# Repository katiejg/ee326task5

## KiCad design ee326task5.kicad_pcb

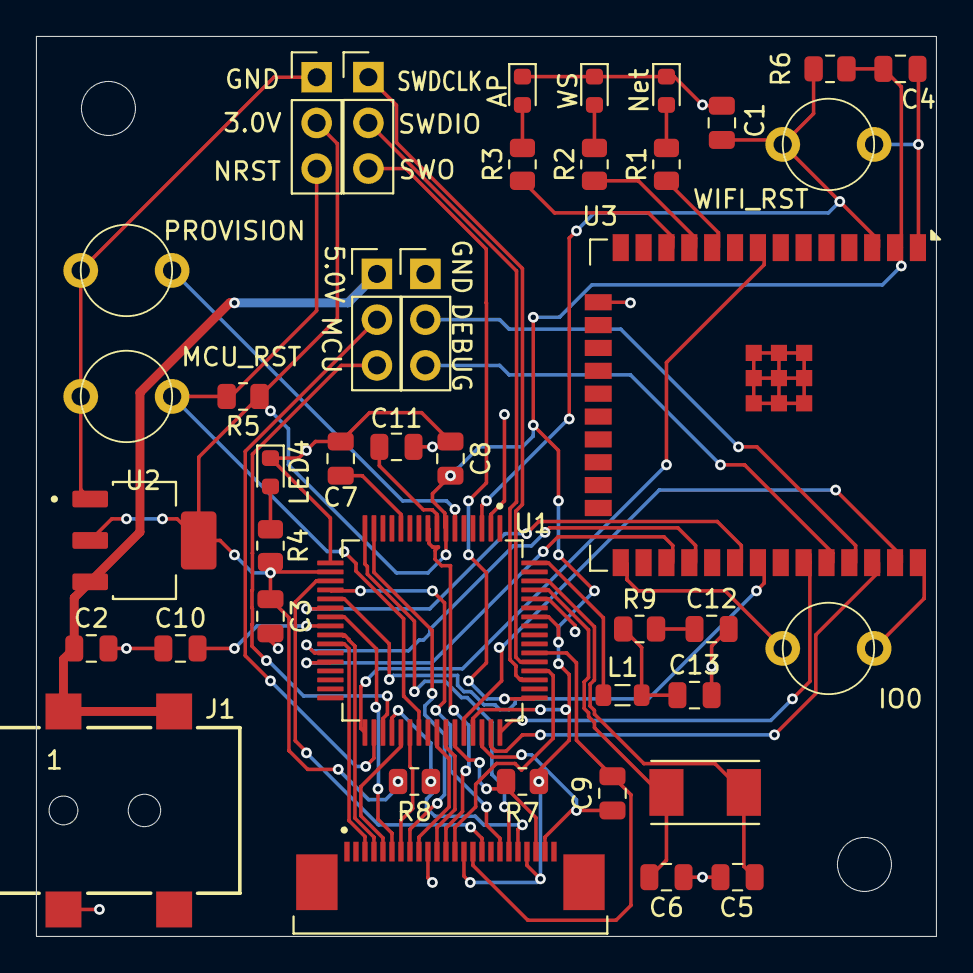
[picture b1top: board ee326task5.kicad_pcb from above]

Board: 2 copper layers, 50.0 x 50.0 mm, 41 parts (0 on the bottom side), 49 nets.

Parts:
AP: RED; LED_0603_1608Metric
C1, C2, C3: 1uF; C_0805_2012Metric
C4, C7, C8, C9, C10, C11, C13: 0.1uF; C_0805_2012Metric
C5, C6: 18pF; C_0805_2012Metric
C12: 4.7uF; C_0805_2012Metric
IO0: IO0; pushbutton
J1: 694106106102
J2, J3, J4, J5: Conn_01x03; PinHeader_1x03_P2.54mm_Vertical
J6: 2-1734592-4; TE_2-1734592-4
L1: 10uH; L_0805_2012Metric
LED4: BLUE; LED_0603_1608Metric
MCU_RST: MCU_RESET; pushbutton
Net: YELLOW; LED_0603_1608Metric
PROVISION: PROVISIONING; pushbutton
R1, R2, R3, R4: 330R; R_0805_2012Metric
R5, R6: 10k; R_0805_2012Metric
R7, R8: 1k; R_0805_2012Metric
R9: 1R0; R_0805_2012Metric
U1: ATSAM4S8BA-AU; QFP50P1200X1200X160-64N
U2: LDL1117S30R; SOT230P700X180-4N
U3: ESP32-WROOM-32; ESP32-WROOM-32E
WIFI_RST: WIFI_RESET; pushbutton
WS: GREEN; LED_0603_1608Metric
Y1: ABM7-12.000MHZ-D2Y-T; XTAL_ABM7-12.000MHZ-D2Y-T

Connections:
+5V: C2.1, J1.1, J1.A1, J4.1, U2.3 (VIN)
/CAM_RST: J6.19, U1.16 (PA20/PGMD8/AD3)
/D0: J6.6, U1.23 (PA24/PGMD12)
/D1: J6.4, U1.25 (PA25/PGMD13)
/D2: J6.3, U1.26 (PA26/PGMD14)
/D3: J6.5, U1.37 (PA27/PGMD15)
/D4: J6.7, U1.38 (PA28)
/D5: J6.9, U1.41 (PA29)
/D6: J6.11, U1.42 (PA30)
/D7: J6.13, U1.52 (PA31)
/DEBUG_RX: J5.3, U3.34 (RXD0/IO3)
/DEBUG_TX: J5.2, U3.35 (TXD0/IO1)
/EN: C1.1, R6.2, U1.3 (PB0/AD4), U3.3 (EN), WIFI_RST.1
/HREF: J6.16, U1.19 (PA16/PGMD4)
/IO0: IO0.1, U3.25 (IO0)
/IO25: R1.1, U3.10 (IO25)
/IO26: R2.1, U3.11 (IO26)
/IO27: R3.1, U3.12 (IO27)
/MCU_RX: J4.3, U1.35 (PA5/PGMRDY)
/MCU_TX: J4.2, U1.34 (PA6/PGMNOE)
/MISO: U1.27 (PA12/PGMD0), U3.28 (IO17)
/MOSI: U1.22 (PA13/PGMD1), U3.30 (IO18)
/NPCS0: U1.28 (PA11/PGMM3), U3.27 (IO16)
/NRST: J3.3, MCU_RST.1, R5.2, U1.39 (~NRST)
/PA0: U1.48 (PA0/PGMEN0), U3.33 (IO21)
/PA1: U1.47 (PA1/PGMEN1), U3.36 (IO22)
/PA2: U1.44 (PA2/PGMEN2), U3.37 (IO23)
/PB3: PROVISION.1, U1.6 (PB3/AD7)
/PB4: U1.33 (TDI/PB4), U3.8 (IO32)
/PCLK: J6.8, U1.15 (PA23/PGMD11)
/SCK: U1.21 (PA14/PGMD2), U3.31 (IO19)
/SCL: J6.20, R8.1, U1.36 (PA4/PGMNCMD)
/SDA: J6.22, R7.1, U1.43 (PA3)
/SWDCLK: J2.1, U1.53 (TCK/SWCLK/PB7)
/SWDIO: J2.2, U1.51 (TMS/SWDIO/PB6)
/SWO: J2.3, U1.49 (TDO/TRACESWO/PB5)
/VDD1V2: C7.2, C9.2, C10.2, C11.2, J6.15, L1.1, U1.8 (VDDOUT), U1.12 (VDDCORE), U1.24 (VDDCORE__1), U1.54 (VDDCORE__2), U1.64 (VDDPLL)
/VDD3V0: C3.1, C4.1, C8.2, J3.2, J6.14, J6.21, R4.1, R5.1, R6.1, R7.2, R8.2, U1.7 (VDDIN), U1.18 (VDDIO), U1.45 (VDDIO__1), U1.58 (VDDIO__2), U2.2 (VOUT), U2.4 (VOUT__1), U3.2 (VDD)
/VSYNC: J6.18, U1.20 (PA15/PGMD3)
/XCLK: J6.12, U1.9 (PA17/PGMD5/AD0)
/XTAL1: C5.2, U1.62 (XIN/PGMCK/PB9), Y1.1
/XTAL2: C6.2, U1.61 (XOUT/PB8), Y1.2
GND: AP.1 (K), C1.2, C2.2, C3.2, C4.2, C5.1, C6.1, C7.1, C8.1, C9.1, C10.1, C11.1, C12.2, C13.2, IO0.2, J1.2, J3.1, J5.1, J6.10, J6.23, LED4.1 (K), MCU_RST.2, Net.1 (K), PROVISION.2, U1.2 (GND), U1.17 (GND__1), U1.46 (GND__2), U1.60 (GND__3), U2.1 (GND), U3.1 (GND), U3.15 (GND), U3.38 (GND), U3.39 (GND), WIFI_RST.2, WS.1 (K)
unnamed: C12.1, R9.2
unnamed: C13.1, L1.2, R9.1
unnamed: Net.2 (A), R1.2
unnamed: R2.2, WS.2 (A)
unnamed: AP.2 (A), R3.2
unnamed: LED4.2 (A), R4.2

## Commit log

2026-02-15 Started PCB Board
2026-02-16 fixed schematic errors
2026-02-18 routing
2026-02-21 finished
